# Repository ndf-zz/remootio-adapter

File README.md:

# Remootio Adapter "PLC" - Hay Hoist

Adapt a Remootio door opener remote to
a golf buggy motor controller using an
AVR m328pb for remote control of a hay hoist.

## Operation

### Manual Operation

On reception of "down" command, hoist is lowered to P1 height.
If no further commands are received, it will retract to the home
position after the configured feed time minutes have elapsed.

A further "down" command will lower the hoist to the P2 height.

Return to home position on reception of an "up" signal, or
after a programmable duration without input.

### Automated Feeding

If a number of feeds per week is specified, the hoist will lower
from the home position to P1 after a randomly chosen interval,
roughly "feeds/week" times a week and provided there is enough
charge in the battery to retract.

The hoist will remain at P1 until feed time minutes have elapsed, 
then retract to the home position. Manual operation "down" or
"up" will cancel a pending automatic operation.

To disable automated feeding, manually lower the hoist slightly
from the home position. To re-enable, return hoist to home
("open") position.

### Special Cases

If an error condition is flagged, the hoist will only allow
movement up and down small amounts determined by the "Man time"
setting. To correct an error state, clear the sensor
switch and then manually operate the hoist down slightly and
then up to the home position.

Errors and exceptions may be triggered by the following conditions:

   - Low Battery: Automated feeding is suppressed when battery
     voltage falls below 13V. In this state, manual operation
     is still enabled. If the battery falls below 11.8V,
     a warning LED is illuminated and remootio operation is disabled.
   - Spurious Sensor: In the case of a spurious triggering of
     the home sensor, an error condition is flagged and the
     motor is stopped.
   - Not at Home: If the home sensor is prematurely
     triggered, the hoist will attempt to continue retraction
     after Home-Retry seconds.
   - Sensor Failure: If the home sensor fails "open", or if the
     state logic is out of sync, the hoist will not react to
     up (raise) commands. If the sensor fails "closed", and max
     H time has elapsed, the hoist will flag an error condition.
   - Safetime: If the hoist is left at position P2, between P1 and P2,
     or in the STOP state, it will attempt to retract automatically
     to the home position after about 60 minutes.
   - Disable Automation: Automated random feeding may be temporarily
     disabled by manually lowering the hoist slightly from the home
     position to state "STOP H-P1". To re-enable random feeding, return
     hoist to home position.

### Serial Console

**Note**: Serial console is not available on units supplied with
BLE adapter.

Connect RS-232 serial adapter to J4 (console)
and open a terminal at 19200 baud, 8n1.

Enter 'p' followed by pin number and enter to enable
console.

Triggers, state changes and errors will
be displayed.

Enter '?' to display available commands:

	Commands:
	        1       H-P1 (0.01s)
	        2       P1-P2 (0.01s)
	        m       Man (0.01s)
	        h       H (0.01s)
	        r       H-Retry (0.01s)
	        f       Feed (minutes)
	        n       Feeds/week (0=off)
	        v       Show values
	        s       Status
	        d       Lower
	        u       Raise

Configuration parameters are adjusted
by entering the command key followed by
an updated value and then enter.
Time values 1,2,m,h and r are set in units of 0.01s.
Feeding time f is in minutes.

## Connectors

Adapter | Connector | Description
--- | --- | ---
J1:1 |  | "S5" Auxiliary I/O (unused)
J1:2 |  | "GND"
J1:3 |  | "S6" Auxiliary I/O (unused)
J1:4 |  | "GND"
N/C | C3:B | Motor + (blue/black)
N/C | C3:C | Motor - (yellow/red)
J2:1 | C4:D | "+12V" Battery + (red)
J2:2 | C4:A | "0V" Battery - (black)
J3:1 |  | ICSP MISO
J3:2 |  | ICSP VCC
J3:3 |  | ICSP SCK
J3:4 |  | ICSP MOSI
J3:5 |  | ICSP RST
J3:6 |  | ICSP GND
J4:1 | C1:2 | "RxD" Console DCE Received Data (brown)
J4:2 | C1:3 | "TxD" Console DCE Transmitted Data (yellow)
J4:3 | C1:5 | "GND" Console DCE Common Ground (white)
J5:1 | C2:C | "Home" Home Limit Input (NC output green)
N/C | C2:B | Short to C2:D (green)
J5:2 | C2:A | "GND" Home Limit Ground (blue)
N/C | C2:D | Short to C2:B
J5:3 |  | "AUX" Encoder/Counter Input (unused)
J5:4 |  | "GND" Encoder/Counter Ground
J6:1 | M1:7 | "PWR" Controller power (pink)
J6:2 | M:6,20 | "GND" Controller ground (black)
J6:3 | M:3 | "Throttle" Controller speed (green)
J6:4 | M:12 | "FWD" Controller forward (white)
J6:5 | M:14 | "REV" Controller reverse (orange)
J6:6 | M:Rx | "Rx" Controller serial receive (blue)
J6:7 | M:Tx | "Tx" Controller serial transmit (green)
J6:8 | M:Gnd | "GND" Controller ground (black)

## Firmware

### Source Layout

	Main event loop:		src/main.c: 	main()
	State machine logic:	src/main.c:		update_state()
	Reset/initialisation:	src/system.c:	system_init()
	Serial console logic:	src/console.c:	read_input()
	SPM controller setting:	src/spmcheck.c	spm_check()

### Version Summaries

   - 25003: BLE adapter updates, October 2025
      - include system clock with state summary
      - adjust low battery override states
      - extend console idle timeout to 5 minutes
      - extend safe time to 60 minutes
   - 25002: Version 2.1, ignore home trigger when at P1
   - 25001: Version 2
      - include Home Retry option & logic
      - add trivial plaintext 'passkey' to protect serial console
   - 24012: Version 1, cosmetic updates for GUI tool, October 2024
   - 24011: Version 0, initial release September 2024

## Build

Connect AVR ISP to programming header, program fuses, initialise
the random seed book, then build and upload firmware to MCU:

	$ make fuse
	$ make randbook
	$ make upload

Note: randbook will overwrite any stored configuration, so it should
only be run once when initialising a new unit. Uploading a new
firmware will not overwrite stored configuration.

On boot, the SPM controller will be updated if required. Updates are
reported to the console output:

	Info: Boot v24011
	SPM: Config updated
	Info: Boot v24011
	SPM: 23014810
	Trigger: reset
	State: [STOP] Batt: 0.0V
	Trigger: home
	[...]

## Build Requirements

   - GNU Make
   - gcc-avr
   - binutils-avr
   - avr-libc
   - avrdude
   - python3 (if controller config is edited)

On a Debian system, use make to install required packages:

	$ make requires

## Production Unit Info

   - [assembly/](assembly/ "Assembly instruction")
   - [assembly/burn-in.sh](assembly/burn-in.sh "Burn-in"):
     Prepare unit for first-time use.
   - [assembly/update25001.sh](assembly/update25001.sh "Update to v25001+"):
     Update unit with firmware < v25001, retaining configuration.

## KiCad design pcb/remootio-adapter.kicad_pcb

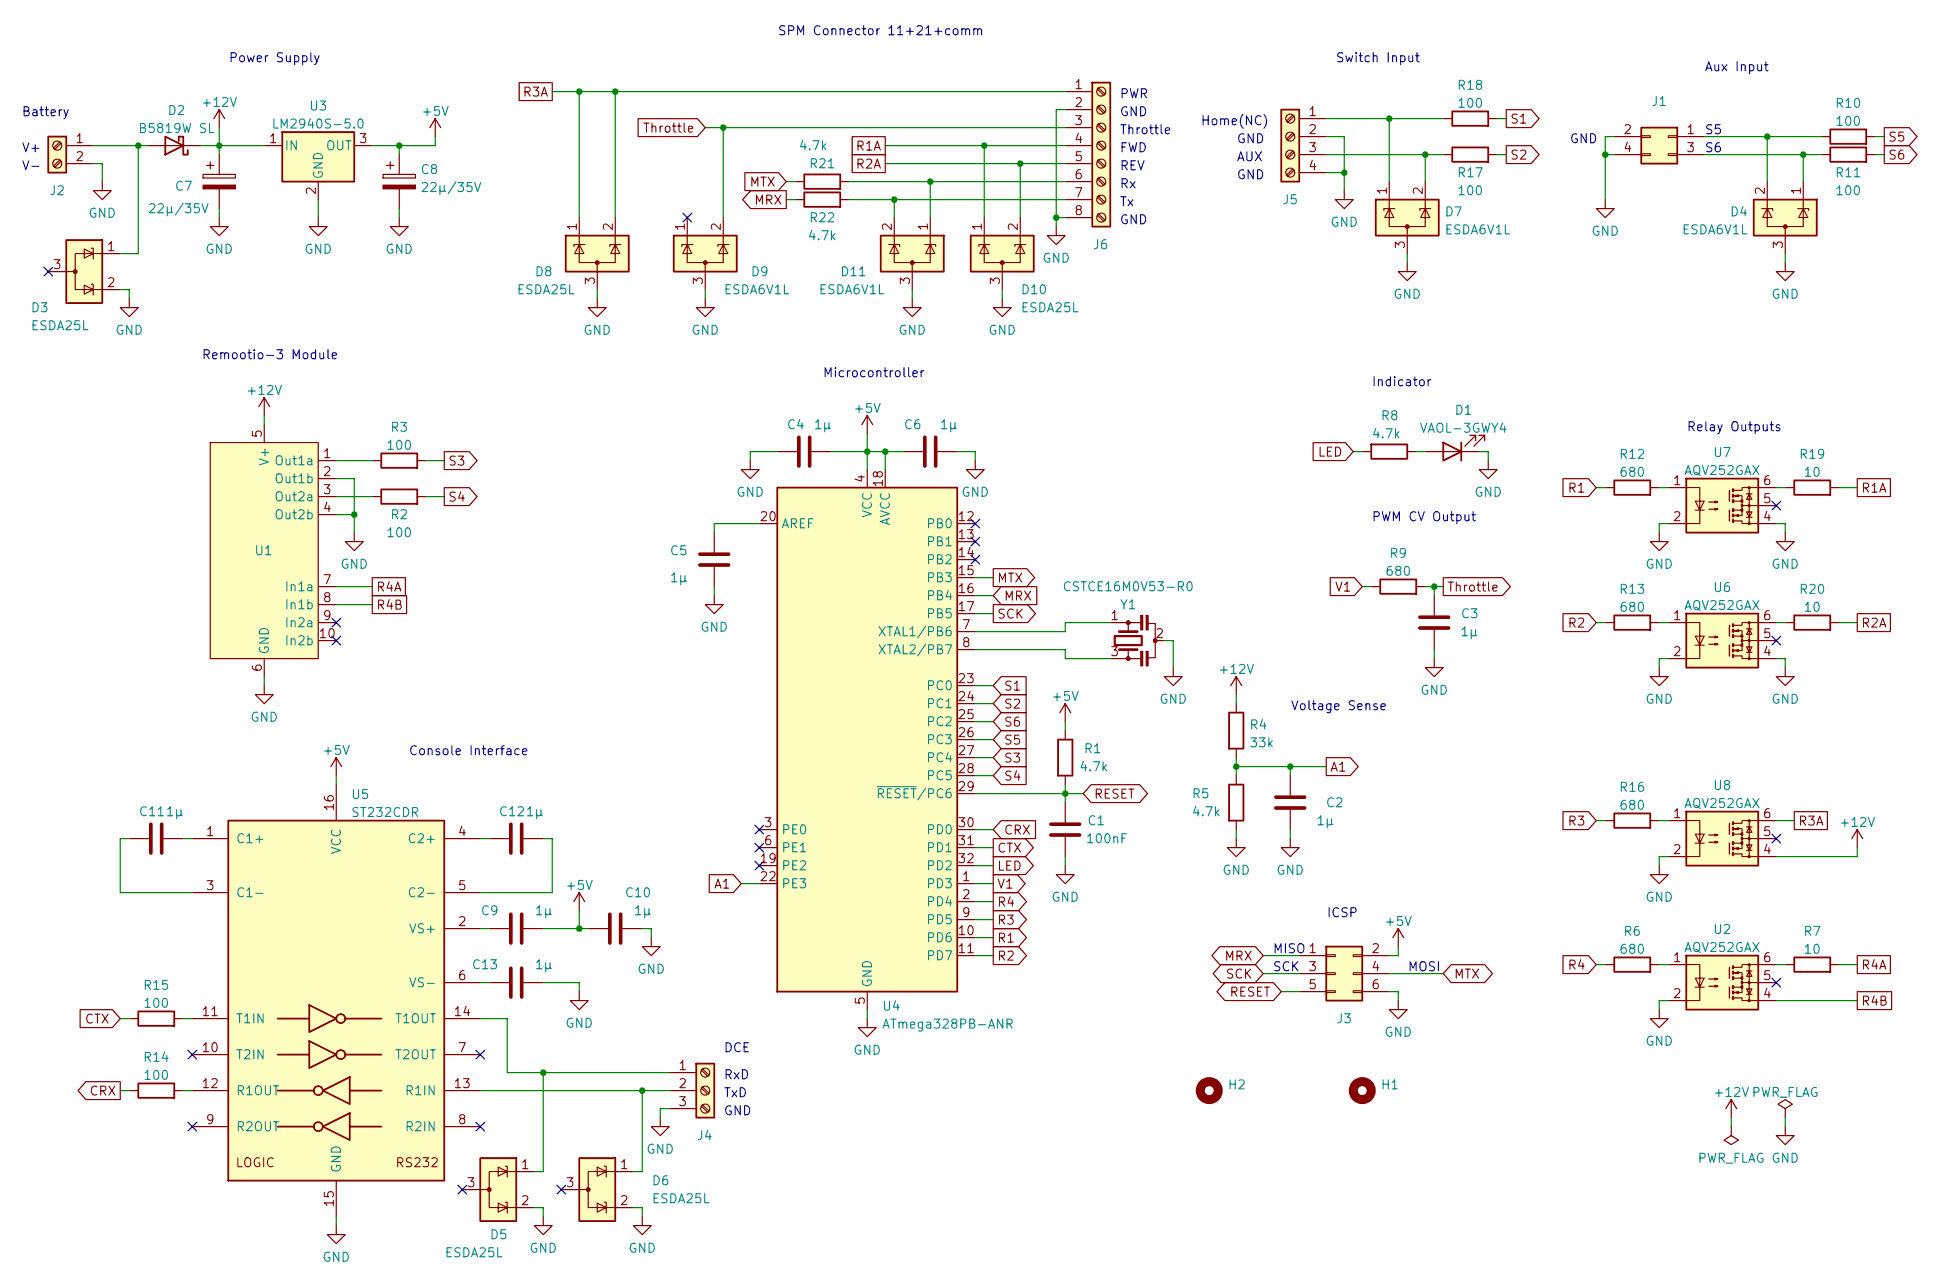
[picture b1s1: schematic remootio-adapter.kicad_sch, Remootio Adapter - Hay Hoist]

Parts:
C1: 100nF; C_0603_1608Metric; PARTNO CC0603KRX7R9BB104; LCSC C14663
C2, C3, C4, C5, C6, C9, C10, C11, C12, C13: 1µ; C_0603_1608Metric; PARTNO GRM188R71E105KA12D; LCSC C86020
C7, C8: 22µ/35V; CP_Elec_5x5.8; PARTNO EEEFN1V220R; LCSC C494835
D1: VAOL-3GWY4; bivar-led
D2: B5819W SL; D_SOD-123; LCSC C8598
D3, D5, D6, D8, D10: ESDA25L; SOT-23; LCSC C95343
D4, D7, D9, D11: ESDA6V1L; SOT-23; LCSC C24378
H1, H2: MountingHole; MountingHole_3.2mm_M3
J1: AUX; PinHeader_2x02_P2.54mm_Vertical; Partno DNP
J2: BATT; TerminalBlock_Phoenix_PT-1,5-2-5.0-H_1x02_P5.00mm_Horizontal; Partno 1935161
J3: ICSP; PinHeader_2x03_P2.54mm_Vertical; Partno 702871099
J4: Console; TerminalBlock_Phoenix_PT-1,5-3-5.0-H_1x03_P5.00mm_Horizontal; Partno 1935174
J5: SwitchIn; TerminalBlock_Phoenix_PT-1,5-4-5.0-H_1x04_P5.00mm_Horizontal; Partno 1935187
J6: SPM Connector; TerminalBlock_Phoenix_PT-1,5-8-5.0-H_1x08_P5.00mm_Horizontal
R1, R5, R8, R21, R22: 4.7k; R_0603_1608Metric; PARTNO 0603WAF4701T5E; LCSC C23162
R2, R3, R10, R11, R14, R15, R17, R18: 100; R_0603_1608Metric; PARTNO GRM188R71E105KA12D; LCSC C22775
R4: 33k; R_0603_1608Metric; PARTNO 0603WAF3302T5E; LCSC C4216
R6, R9, R12, R13, R16: 680; R_0603_1608Metric; PARTNO 0603WAF6800T5E; LCSC C23228
R7, R19, R20: 10; R_0603_1608Metric; PARTNO 0603WAF100JT5E; LCSC C22859
U1: remootio-3
U2, U6, U7, U8: AQV252GAX; SMDIP-6_W7.62mm; LCSC C425149
U3: LM2940S-5.0; SOT-223-3_TabPin2; LCSC C596334
U4: ATmega328PB-ANR; TQFP-32_7x7mm_P0.8mm; LCSC C2053137
U5: ST232CDR; SO-16_3.9x9.9mm_P1.27mm; LCSC C6869
Y1: CSTCE16M0V53-R0; Resonator_SMD_Murata_CSTxExxV-3Pin_3.0x1.1mm; LCSC C32180

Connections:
+5V: C4.1, C6.2, C8.1, C9.1, C10.2, J3.2, R1.1, U3.3 (OUT), U4.4 (VCC), U4.18 (AVCC), U5.16 (VCC)
+12V: C7.1, D2.1 (K), R4.1, U1.5 (V+), U3.1 (IN), U8.4
A1: C2.2, R4.2, R5.1, U4.22 (PE3)
CRX: R14.1, U4.30 (PD0)
CTX: R15.1, U4.31 (PD1)
GND: C1.1, C2.1, C3.1, C4.2, C5.2, C6.1, C7.2, C8.2, C10.1, C13.1, D1.1 (K), D3.2 (K), D4.3 (A), D5.2 (K), D6.2 (K), D7.3 (A), D8.3 (A), D9.3 (A), D10.3 (A), D11.3 (A), J1.2, J1.4, J2.2, J3.6, J4.3, J5.2, J5.4, J6.2, J6.8, R5.2, U1.2 (Out1b), U1.4 (Out2b), U1.6 (GND), U2.2, U3.2 (GND), U4.5 (GND), U4.21 (GND), U5.15 (GND), U6.2, U6.4, U7.2, U7.4, U8.2, Y1.2
LED: R8.2, U4.32 (PD2)
MRX: J3.1, R22.1, U4.16 (PB4)
MTX: J3.4, R21.1, U4.15 (PB3)
unnamed: C5.1, U4.20 (AREF)
unnamed: C9.2, U5.2 (VS+)
unnamed: C11.1, U5.1 (C1+)
unnamed: C11.2, U5.3 (C1-)
unnamed: C12.1, U5.5 (C2-)
unnamed: C12.2, U5.4 (C2+)
unnamed: C13.2, U5.6 (VS-)
unnamed: D1.2 (A), R8.1
unnamed: D2.2 (A), D3.1 (K), J2.1
unnamed: D4.1 (K), J1.3, R11.1
unnamed: D4.2 (K), J1.1, R10.1
unnamed: D5.1 (K), J4.1, U5.14 (T1OUT)
unnamed: D6.1 (K), J4.2, U5.13 (R1IN)
unnamed: D7.1 (K), J5.1, R18.1
unnamed: D7.2 (K), J5.3, R17.1
unnamed: D11.1 (K), J6.6, R21.2
unnamed: D11.2 (K), J6.7, R22.2
unnamed: R2.1, U1.3 (Out2a)
unnamed: R3.1, U1.1 (Out1a)
unnamed: R6.2, U2.1
unnamed: R7.1, U2.6
unnamed: R12.2, U7.1
unnamed: R13.2, U6.1
unnamed: R14.2, U5.12 (R1OUT)
unnamed: R15.2, U5.11 (T1IN)
unnamed: R16.2, U8.1
unnamed: R19.1, U7.6
unnamed: R20.1, U6.6
unnamed: U4.7 (XTAL1/PB6), Y1.1
unnamed: U4.8 (XTAL2/PB7), Y1.3
R1: R12.1, U4.10 (PD6)
R1A: D10.1 (K), J6.4, R19.2
R2: R13.1, U4.11 (PD7)
R2A: D10.2 (K), J6.5, R20.2
R3: R16.1, U4.9 (PD5)
R3A: D8.1 (K), D8.2 (K), J6.1, U8.6
R4: R6.1, U4.2 (PD4)
R4A: R7.2, U1.7 (In1a)
R4B: U1.8 (In1b), U2.4
RESET: C1.2, J3.5, R1.2, U4.29 (~RESET/PC6)
S1: R18.2, U4.23 (PC0)
S2: R17.2, U4.24 (PC1)
S3: R3.2, U4.27 (PC4)
S4: R2.2, U4.28 (PC5)
S5: R10.2, U4.26 (PC3)
S6: R11.2, U4.25 (PC2)
SCK: J3.3, U4.17 (PB5)
Throttle: C3.2, D9.2 (K), J6.3, R9.2
V1: R9.1, U4.1 (PD3)

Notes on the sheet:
Microcontroller
GND
Voltage Sense
SCK
MOSI
PWM CV Output
Relay Outputs
Power Supply
ICSP
SPM Connector 11+21+comm
REV
MISO
Throttle
Switch Input
Remootio-3 Module
FWD
Battery
DCE
Home(NC)
TxD
Console Interface
Aux Input
PWR
AUX
Indicator
RxD

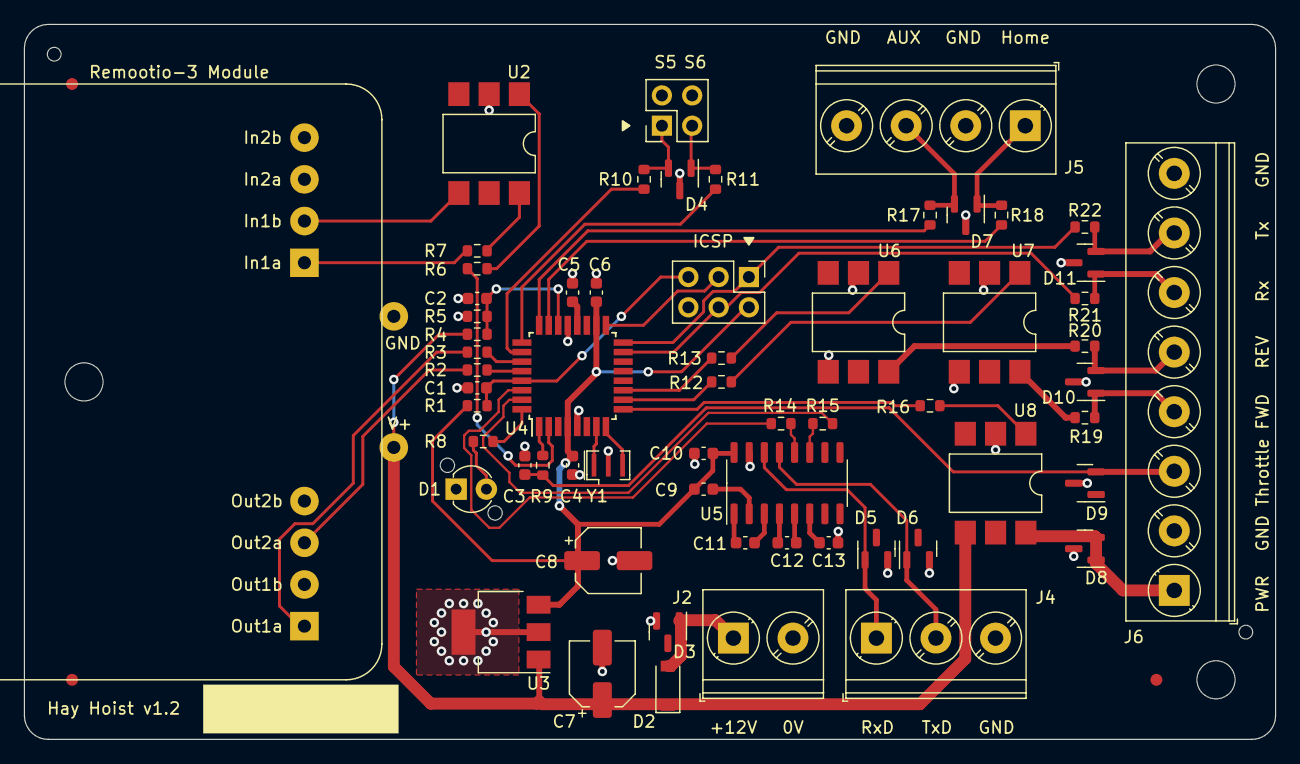
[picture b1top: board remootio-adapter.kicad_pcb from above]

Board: 2 copper layers, 105.0 x 60.0 mm, 63 parts (0 on the bottom side), 58 nets.

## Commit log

2024-05-29 Add files
2024-06-13 Add random codebook to eeprom
2024-06-13 Ignore datasheets and prototype layout
2024-06-13 Functional prototype upgrade
2024-06-13 Update state diagram
2024-07-03 Indicate P1/home to remootio and return to home after timeout in p2 or stop
2024-07-05 Simplify counters and report all values
2024-07-05 Suppress feed message when disabled
2024-07-22 Add v1.0/m328pb PCB
2024-07-22 Add watchdog timer to main loop
2024-07-22 Remove brake cv and update low voltage logic
2024-07-22 Update prototype docs to match final version
2024-07-25 Document special case logic and remove duplicate motor delay
2024-07-28 Add spmtool config file and update readme
2024-07-28 Fix typo
2024-07-30 Update for m328pb and final PCB layout
2024-07-30 Revise PCB layout for production board v1.1
2024-07-31 Add mounting hole diagram
2024-08-06 Minor cosmetic footprint adjustment
2024-08-06 Jostle footprints onto 0.5mm grid and change terminals to 5mm pitch
2024-08-06 Adjust motor controller settings at boot if required
2024-08-07 Change console to 19200 baud
2024-08-07 Replace C7 and C8 with EEEFN1V220R
2024-08-13 Avoid reboot loop on failed spm setting
2024-08-13 Update readme with connector info
2024-08-13 Add part nos for screw terminals
2024-08-14 Add delay after motor off and reduce max battery current to 85%
2024-08-14 Fix table typo
2024-08-16 Alter remootio power pads and add fiducials
2024-08-16 Add basic mech hole footprint
2024-08-16 Adjust default values and remove superfluous stop
2024-08-27 Begin assembly instruction
2024-08-27 Add missing connector images
2024-08-28 Add motor controller preparation
2024-09-28 Alter auto mode to per week instead of day, update default values
2024-09-28 Update assembly instruction
2024-10-13 Add configuration tool
2024-10-13 Cosmetic updates for config utils
2024-10-15 Add graphical config tool
2024-10-15 Fix logic error in set event, add logo image
2024-12-07 Update logo image to PNG
2024-12-08 Fix config key filter mismatch
2024-12-08 Update screenshot
2024-12-08 HH Config v1.0.2: Add tool tips and fix disconnect error
2025-04-11 v25001 home retry and console PIN
2025-04-11 Update config tool
2025-04-11 Update documentation for v25001
2025-04-13 Update BTC connect logic
2025-04-17 Suppress options by firmware version
2025-04-17 Ignore home trigger at P1
2025-06-26 Remove broken command line config tool
2025-06-27 Use spinbox for position timers
2025-09-09 Remove BT classic intrface
2025-09-09 Include firmware update with eeprom patch script
2025-10-02 Firmware v25003
2025-10-02 Update README for v25003
2025-10-02 Fix typos
2025-10-04 Add Bluetooth config utility
2025-10-04 Rename screenshot file
